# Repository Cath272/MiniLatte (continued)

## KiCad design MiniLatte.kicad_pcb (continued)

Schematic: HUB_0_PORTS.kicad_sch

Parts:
C19, C20, C21, C22, C23, C24, C25, C26: 100nF; C_0402_1005Metric
C85, C86, C87: 220uF; C_Elec_6.3x7.7
D11, D12, D13, D14: RCLAMP0524P-N; DFN-10L_L2.5-W1.0-P0.50-BL; LCSC Part C316044
R11: 120k; R_0402_1005Metric
R12, R13: 10k; R_0402_1005Metric
R27, R28: ?k; R_0402_1005Metric
U3: VL162; MQFN-28_L4.5-W3.5-P0.40-BL-EP; LCSC Part C19270896
U8: TPS2560DRCR; VSON-10_L3.0-W3.0-P0.50-BL-EP_TPS62410DRCR; LCSC Part C140304
U9: TPS2553DRVR-1; WSON-6_L2.0-W2.0-P0.65-BL-EP; LCSC Part C411878
USB1: TYPEC-324-BCP24; USB-C-SMD_TYPEC-324-BCP24; LCSC Part C2835314
USB2, USB3: U-A-39WD-W-1; USB-A-SMD_U-A-39WD-W-1; LCSC Part C3020886

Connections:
+5V: U3.25 (CE), U3.26 (VCC5V), U3.27 (Vconn_5Vin), U8.2 (IN), U8.3 (IN), U9.6 (IN); also elsewhere on the board
+5V_DFP2: C87.1, USB1.A4 (VBUS), USB1.A9 (VBUS), USB1.B4 (VBUS), USB1.B9 (VBUS); also elsewhere on the board
+5V_DFP3: C85.1, USB3.1 (VBUS); also elsewhere on the board
+5V_DFP4: C86.1, USB2.1 (VBUS); also elsewhere on the board
+5V_H0_DFP1: U8.9 (OUT1)
+5V_H0_DFP2: U8.8 (OUT2)
+5V_H0_DFP3: U9.1 (OUT)
/USB_3/USB_HUB_0/HUB_0_PORTS/DFP2TX1+: C19.2, U3.2 (TX1_P)
/USB_3/USB_HUB_0/HUB_0_PORTS/DFP2TX1-: C20.1, U3.3 (TX1_N)
/USB_3/USB_HUB_0/HUB_0_PORTS/DFP2TX2+: C22.1, U3.5 (TX2_P)
/USB_3/USB_HUB_0/HUB_0_PORTS/DFP2TX2-: C21.2, U3.4 (TX2_N)
/USB_3/USB_HUB_0/HUB_0_PORTS/DFP2_D+: USB1.A6 (DP1), USB1.B6 (DP2); also elsewhere on the board
/USB_3/USB_HUB_0/HUB_0_PORTS/DFP2_D-: USB1.A7 (DN1), USB1.B7 (DN2); also elsewhere on the board
/USB_3/USB_HUB_0/HUB_0_PORTS/DFP2_RX+: U3.18 (RX_P); also elsewhere on the board
/USB_3/USB_HUB_0/HUB_0_PORTS/DFP2_RX-: U3.17 (RX_N); also elsewhere on the board
/USB_3/USB_HUB_0/HUB_0_PORTS/DFP2_TX+: U3.21 (TXP); also elsewhere on the board
/USB_3/USB_HUB_0/HUB_0_PORTS/DFP2_TX-: U3.20 (TXN); also elsewhere on the board
/USB_3/USB_HUB_0/HUB_0_PORTS/DFP3_D+: USB3.3 (D+); also elsewhere on the board
/USB_3/USB_HUB_0/HUB_0_PORTS/DFP3_D-: USB3.2 (D-); also elsewhere on the board
/USB_3/USB_HUB_0/HUB_0_PORTS/DFP3_RX+: D13.2, D13.9, USB3.6 (STDA_SSRX+); also elsewhere on the board
/USB_3/USB_HUB_0/HUB_0_PORTS/DFP3_RX-: D13.1, D13.10, USB3.5 (STDA_SSRX-); also elsewhere on the board
/USB_3/USB_HUB_0/HUB_0_PORTS/DFP3_TX+: C26.2; also elsewhere on the board
/USB_3/USB_HUB_0/HUB_0_PORTS/DFP3_TX-: C25.1; also elsewhere on the board
/USB_3/USB_HUB_0/HUB_0_PORTS/DFP4_D+: USB2.3 (D+); also elsewhere on the board
/USB_3/USB_HUB_0/HUB_0_PORTS/DFP4_D-: USB2.2 (D-); also elsewhere on the board
/USB_3/USB_HUB_0/HUB_0_PORTS/DFP4_RX+: D14.2, D14.9, USB2.6 (STDA_SSRX+); also elsewhere on the board
/USB_3/USB_HUB_0/HUB_0_PORTS/DFP4_RX-: D14.1, D14.10, USB2.5 (STDA_SSRX-); also elsewhere on the board
/USB_3/USB_HUB_0/HUB_0_PORTS/DFP4_TX+: C24.2; also elsewhere on the board
/USB_3/USB_HUB_0/HUB_0_PORTS/DFP4_TX-: C23.1; also elsewhere on the board
/USB_3/USB_HUB_0/HUB_0_PORTS/H0_DFP3TXC+: C26.1, D13.5, D13.6, USB3.9 (STDA_SSTX+)
/USB_3/USB_HUB_0/HUB_0_PORTS/H0_DFP3TXC-: C25.2, D13.4, D13.7, USB3.8 (STDA_SSTX-)
/USB_3/USB_HUB_0/HUB_0_PORTS/H0_DFP4TXC+: C24.1, D14.5, D14.6, USB2.9 (STDA_SSTX+)
/USB_3/USB_HUB_0/HUB_0_PORTS/H0_DFP4TXC-: C23.2, D14.4, D14.7, USB2.8 (STDA_SSTX-)
DFP2_H0_RX_1+: D11.1, D11.10, U3.6 (RX1_P), USB1.B11 (SSRXp1)
DFP2_H0_RX_1-: D11.2, D11.9, U3.7 (RX1_N), USB1.B10 (SSRXn1)
DFP2_H0_RX_2+: D12.5, D12.6, U3.9 (RX2_P), USB1.A11 (SSRXp2)
DFP2_H0_RX_2-: D12.4, D12.7, U3.8 (RX2_N), USB1.A10 (SSRXn2)
DFP2_H0_TX_1+: D12.1, D12.10, USB1.A2 (SSTXP1)
DFP2_H0_TX_1-: D12.2, D12.9, USB1.A3 (SSTXn1)
DFP2_H0_TX_2+: D11.5, D11.6, USB1.B2 (SSTXp2)
DFP2_H0_TX_2-: D11.4, D11.7, USB1.B3 (SSTXn2)
DFP2_TX_1+: C19.1
DFP2_TX_1-: C20.2
DFP2_TX_2+: C22.2
DFP2_TX_2-: C21.1
GND: C85.2, C86.2, C87.2, D11.3, D11.8, D12.3, D12.8, D13.3, D13.8, D14.3, D14.8, R11.1, R12.2, R13.2, R27.1, R28.1, U3.19 (GND), U3.29 (EP), U8.1 (GND), U8.11 (EPAD), U9.5 (GND), U9.7 (EP), USB1.1 (EP), USB1.2 (EP), USB1.3 (EP), USB1.4 (EP), USB1.A1 (GND), USB1.A12 (GND), USB1.B1 (GND), USB1.B12 (GND), USB2.4 (GND), USB2.7 (GND_DRAIN), USB2.10 (EP), USB2.11 (EP), USB3.4 (GND), USB3.7 (GND_DRAIN), USB3.10 (EP), USB3.11 (EP); also elsewhere on the board
H0_CC1_DFP2: U3.1 (CC1), USB1.A5 (CC1)
H0_CC2_DFP2: U3.28 (CC2), USB1.B5 (CC2)
H0_USBOC1: U8.10 (~FAULT1)
H0_USBOC2: U8.6 (~FAULT2); also elsewhere on the board
H0_USBOC3: U9.3 (~FAULT); also elsewhere on the board
H0_USBPE1: U8.4 (EN1)
H0_USBPE2: U8.5 (EN2); also elsewhere on the board
H0_USBPE3: U9.4 (EN); also elsewhere on the board
unnamed: R12.1, U3.24 (CurrentSettingin<0>)
unnamed: R13.1, U3.23 (CurrentSettingin<1>)
unnamed: R11.2, U3.10 (REXT)
unnamed: R27.2, U8.7 (ILIM)
unnamed: R28.2, U9.2 (ILIM)

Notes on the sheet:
TO ADD CAPS ON TX LINES + TO ADD TVS DIODE

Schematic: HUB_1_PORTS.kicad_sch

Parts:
C88, C89: 220uF; C_Elec_6.3x7.7
C120, C121, C122, C123, C124, C125, C126, C127, C166, C174, C175, C176: 100nF; C_0402_1005Metric
D15, D16: RCLAMP0524P-N; DFN-10L_L2.5-W1.0-P0.50-BL; LCSC Part C316044
R54, R107: 120k; R_0402_1005Metric
R55, R56, R108, R109: 10k; R_0402_1005Metric
R111, R112: ?k; R_0402_1005Metric
U13, U18: VL162; MQFN-28_L4.5-W3.5-P0.40-BL-EP; LCSC Part C19270896
U20, U21: TPS2560DRCR; VSON-10_L3.0-W3.0-P0.50-BL-EP_TPS62410DRCR; LCSC Part C140304
USB9: USB-303WSD-BRY; USB-A-TH_XUNPU_USB-303WSD-BRY; LCSC Part C2895028

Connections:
+5V: U13.25 (CE), U13.26 (VCC5V), U13.27 (Vconn_5Vin), U18.25 (CE), U18.26 (VCC5V), U18.27 (Vconn_5Vin), U20.2 (IN), U20.3 (IN), U21.2 (IN), U21.3 (IN); also elsewhere on the board
+5V_DFP3: C89.1, USB9.10 (VBUS2); also elsewhere on the board
+5V_DFP4: C88.1, USB9.1 (VBUS1); also elsewhere on the board
+5V_H1_DFP1: U20.9 (OUT1)
+5V_H1_DFP2: U20.8 (OUT2)
+5V_H1_DFP3: U21.9 (OUT1)
+5V_H1_DFP4: U21.8 (OUT2)
/USB_3/USB_HUB_1/HUB_1_PORTS/DFP1_RX+: U18.18 (RX_P); also elsewhere on the board
/USB_3/USB_HUB_1/HUB_1_PORTS/DFP1_RX-: U18.17 (RX_N); also elsewhere on the board
/USB_3/USB_HUB_1/HUB_1_PORTS/DFP1_TX+: U18.21 (TXP); also elsewhere on the board
/USB_3/USB_HUB_1/HUB_1_PORTS/DFP1_TX-: U18.20 (TXN); also elsewhere on the board
/USB_3/USB_HUB_1/HUB_1_PORTS/DFP2_RX+: U13.18 (RX_P); also elsewhere on the board
/USB_3/USB_HUB_1/HUB_1_PORTS/DFP2_RX-: U13.17 (RX_N); also elsewhere on the board
/USB_3/USB_HUB_1/HUB_1_PORTS/DFP2_TX+: U13.21 (TXP); also elsewhere on the board
/USB_3/USB_HUB_1/HUB_1_PORTS/DFP2_TX-: U13.20 (TXN); also elsewhere on the board
/USB_3/USB_HUB_1/HUB_1_PORTS/DFP3_D+: USB9.12 (D2+); also elsewhere on the board
/USB_3/USB_HUB_1/HUB_1_PORTS/DFP3_D-: USB9.11 (D2-); also elsewhere on the board
/USB_3/USB_HUB_1/HUB_1_PORTS/DFP3_RX+: D15.2, D15.9, USB9.15 (StdA_SSRX2+); also elsewhere on the board
/USB_3/USB_HUB_1/HUB_1_PORTS/DFP3_RX-: D15.1, D15.10, USB9.14 (StdA_SSRX2-); also elsewhere on the board
/USB_3/USB_HUB_1/HUB_1_PORTS/DFP3_TX+: C127.2; also elsewhere on the board
/USB_3/USB_HUB_1/HUB_1_PORTS/DFP3_TX-: C126.1; also elsewhere on the board
/USB_3/USB_HUB_1/HUB_1_PORTS/DFP4_D+: USB9.3 (D1+); also elsewhere on the board
/USB_3/USB_HUB_1/HUB_1_PORTS/DFP4_D-: USB9.2 (D1-); also elsewhere on the board
/USB_3/USB_HUB_1/HUB_1_PORTS/DFP4_RX+: D16.2, D16.9, USB9.6 (StdA_SSRX1+); also elsewhere on the board
/USB_3/USB_HUB_1/HUB_1_PORTS/DFP4_RX-: D16.1, D16.10, USB9.5 (StdA_SSRX1-); also elsewhere on the board
/USB_3/USB_HUB_1/HUB_1_PORTS/DFP4_TX+: C125.2; also elsewhere on the board
/USB_3/USB_HUB_1/HUB_1_PORTS/DFP4_TX-: C124.1; also elsewhere on the board
/USB_3/USB_HUB_1/HUB_1_PORTS/H1_DFP1TX1+: C166.2, U18.2 (TX1_P)
/USB_3/USB_HUB_1/HUB_1_PORTS/H1_DFP1TX1-: C174.1, U18.3 (TX1_N)
/USB_3/USB_HUB_1/HUB_1_PORTS/H1_DFP1TX2+: C176.1, U18.5 (TX2_P)
/USB_3/USB_HUB_1/HUB_1_PORTS/H1_DFP1TX2-: C175.2, U18.4 (TX2_N)
/USB_3/USB_HUB_1/HUB_1_PORTS/H1_DFP2TX1+: C120.2, U13.2 (TX1_P)
/USB_3/USB_HUB_1/HUB_1_PORTS/H1_DFP2TX1-: C121.1, U13.3 (TX1_N)
/USB_3/USB_HUB_1/HUB_1_PORTS/H1_DFP2TX2+: C123.1, U13.5 (TX2_P)
/USB_3/USB_HUB_1/HUB_1_PORTS/H1_DFP2TX2-: C122.2, U13.4 (TX2_N)
/USB_3/USB_HUB_1/HUB_1_PORTS/H1_DFP3TXC+: C127.1, D15.5, D15.6, USB9.18 (StdA_SSTX2+)
/USB_3/USB_HUB_1/HUB_1_PORTS/H1_DFP3TXC-: C126.2, D15.4, D15.7, USB9.17 (StdA_SSTX2-)
/USB_3/USB_HUB_1/HUB_1_PORTS/H1_DFP4TXC+: C125.1, D16.5, D16.6, USB9.9 (StdA_SSTX1+)
/USB_3/USB_HUB_1/HUB_1_PORTS/H1_DFP4TXC-: C124.2, D16.4, D16.7, USB9.8 (StdA_SSTX1-)
GND: C88.2, C89.2, D15.3, D15.8, D16.3, D16.8, R54.1, R55.2, R56.2, R107.1, R108.2, R109.2, R111.1, R112.1, U13.19 (GND), U13.29 (EP), U18.19 (GND), U18.29 (EP), U20.1 (GND), U20.11 (EPAD), U21.1 (GND), U21.11 (EPAD), USB9.4 (GND1), USB9.7 (GND_DRAIN1), USB9.13 (GND2), USB9.16 (GND_DRAIN2), USB9.19 (Shield), USB9.20 (Shield), USB9.21 (Shield), USB9.22 (Shield); also elsewhere on the board
H1_CC1_DFP1: U18.1 (CC1); also elsewhere on the board
H1_CC1_DFP2: U13.1 (CC1); also elsewhere on the board
H1_CC2_DFP1: U18.28 (CC2); also elsewhere on the board
H1_CC2_DFP2: U13.28 (CC2); also elsewhere on the board
H1_DFP1_RX_1+: U18.6 (RX1_P); also elsewhere on the board
H1_DFP1_RX_1-: U18.7 (RX1_N); also elsewhere on the board
H1_DFP1_RX_2+: U18.9 (RX2_P); also elsewhere on the board
H1_DFP1_RX_2-: U18.8 (RX2_N); also elsewhere on the board
H1_DFP1_TX_1+: C166.1; also elsewhere on the board
H1_DFP1_TX_1-: C174.2; also elsewhere on the board
H1_DFP1_TX_2+: C176.2; also elsewhere on the board
H1_DFP1_TX_2-: C175.1; also elsewhere on the board
H1_DFP2_RX_1+: U13.6 (RX1_P); also elsewhere on the board
H1_DFP2_RX_1-: U13.7 (RX1_N); also elsewhere on the board
H1_DFP2_RX_2+: U13.9 (RX2_P); also elsewhere on the board
H1_DFP2_RX_2-: U13.8 (RX2_N); also elsewhere on the board
H1_DFP2_TX_1+: C120.1; also elsewhere on the board
H1_DFP2_TX_1-: C121.2; also elsewhere on the board
H1_DFP2_TX_2+: C123.2; also elsewhere on the board
H1_DFP2_TX_2-: C122.1; also elsewhere on the board
H1_USBOC1: U20.10 (~FAULT1)
H1_USBOC2: U20.6 (~FAULT2); also elsewhere on the board
H1_USBOC3: U21.10 (~FAULT1); also elsewhere on the board
H1_USBOC4: U21.6 (~FAULT2); also elsewhere on the board
H1_USBPE1: U20.4 (EN1)
H1_USBPE2: U20.5 (EN2); also elsewhere on the board
H1_USBPE3: U21.4 (EN1); also elsewhere on the board
H1_USBPE4: U21.5 (EN2); also elsewhere on the board
unnamed: R55.1, U13.24 (CurrentSettingin<0>)
unnamed: R56.1, U13.23 (CurrentSettingin<1>)
unnamed: R54.2, U13.10 (REXT)
unnamed: R108.1, U18.24 (CurrentSettingin<0>)
unnamed: R109.1, U18.23 (CurrentSettingin<1>)
unnamed: R107.2, U18.10 (REXT)
unnamed: R111.2, U20.7 (ILIM)
unnamed: R112.2, U21.7 (ILIM)

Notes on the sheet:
TO ADD CAPS ON TX LINES + TO ADD TVS DIODE

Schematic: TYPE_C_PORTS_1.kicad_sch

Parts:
C90, C91: 220uF; C_Elec_6.3x7.7
D7, D8, D9, D10: RCLAMP0524P-N; DFN-10L_L2.5-W1.0-P0.50-BL; LCSC Part C316044
USB4, USB7: TYPEC-324-BCP24; USB-C-SMD_TYPEC-324-BCP24; LCSC Part C2835314

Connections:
+5V_DFP1: C91.1, USB7.A4 (VBUS), USB7.A9 (VBUS), USB7.B4 (VBUS), USB7.B9 (VBUS)
+5V_DFP2: C90.1, USB4.A4 (VBUS), USB4.A9 (VBUS), USB4.B4 (VBUS), USB4.B9 (VBUS); also elsewhere on the board
/USB_3/USB_HUB_1/HUB_1_PORTS/DFP1_D+: USB7.A6 (DP1), USB7.B6 (DP2); also elsewhere on the board
/USB_3/USB_HUB_1/HUB_1_PORTS/DFP1_D-: USB7.A7 (DN1), USB7.B7 (DN2); also elsewhere on the board
/USB_3/USB_HUB_1/HUB_1_PORTS/DFP2_D+: USB4.A6 (DP1), USB4.B6 (DP2); also elsewhere on the board
/USB_3/USB_HUB_1/HUB_1_PORTS/DFP2_D-: USB4.A7 (DN1), USB4.B7 (DN2); also elsewhere on the board
GND: C90.2, C91.2, D7.3, D7.8, D8.3, D8.8, D9.3, D9.8, D10.3, D10.8, USB4.1 (EP), USB4.2 (EP), USB4.3 (EP), USB4.4 (EP), USB4.A1 (GND), USB4.A12 (GND), USB4.B1 (GND), USB4.B12 (GND), USB7.1 (EP), USB7.2 (EP), USB7.3 (EP), USB7.4 (EP), USB7.A1 (GND), USB7.A12 (GND), USB7.B1 (GND), USB7.B12 (GND); also elsewhere on the board
H1_CC1_DFP1: USB7.A5 (CC1); also elsewhere on the board
H1_CC1_DFP2: USB4.A5 (CC1); also elsewhere on the board
H1_CC2_DFP1: USB7.B5 (CC2); also elsewhere on the board
H1_CC2_DFP2: USB4.B5 (CC2); also elsewhere on the board
H1_DFP1_RX_1+: D9.1, D9.10, USB7.B11 (SSRXp1); also elsewhere on the board
H1_DFP1_RX_1-: D9.2, D9.9, USB7.B10 (SSRXn1); also elsewhere on the board
H1_DFP1_RX_2+: D10.5, D10.6, USB7.A11 (SSRXp2); also elsewhere on the board
H1_DFP1_RX_2-: D10.4, D10.7, USB7.A10 (SSRXn2); also elsewhere on the board
H1_DFP1_TX_1+: D10.1, D10.10, USB7.A2 (SSTXP1); also elsewhere on the board
H1_DFP1_TX_1-: D10.2, D10.9, USB7.A3 (SSTXn1); also elsewhere on the board
H1_DFP1_TX_2+: D9.5, D9.6, USB7.B2 (SSTXp2); also elsewhere on the board
H1_DFP1_TX_2-: D9.4, D9.7, USB7.B3 (SSTXn2); also elsewhere on the board
H1_DFP2_RX_1+: D8.1, D8.10, USB4.B11 (SSRXp1); also elsewhere on the board
H1_DFP2_RX_1-: D8.2, D8.9, USB4.B10 (SSRXn1); also elsewhere on the board
H1_DFP2_RX_2+: D8.5, D8.6, USB4.A11 (SSRXp2); also elsewhere on the board
H1_DFP2_RX_2-: D8.4, D8.7, USB4.A10 (SSRXn2); also elsewhere on the board
H1_DFP2_TX_1+: D7.1, D7.10, USB4.A2 (SSTXP1); also elsewhere on the board
H1_DFP2_TX_1-: D7.2, D7.9, USB4.A3 (SSTXn1); also elsewhere on the board
H1_DFP2_TX_2+: D7.5, D7.6, USB4.B2 (SSTXp2); also elsewhere on the board
H1_DFP2_TX_2-: D7.4, D7.7, USB4.B3 (SSTXn2); also elsewhere on the board

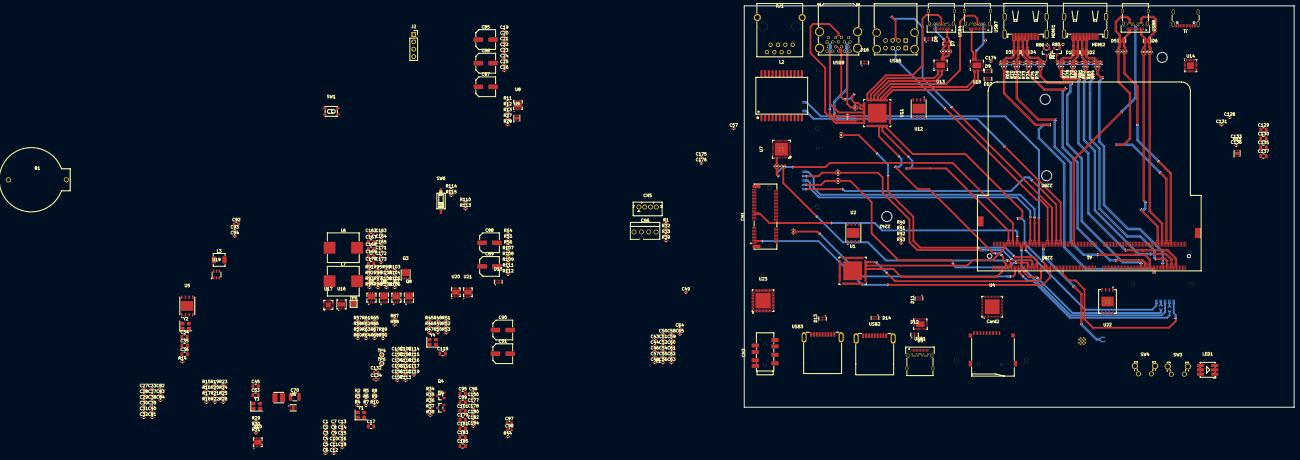
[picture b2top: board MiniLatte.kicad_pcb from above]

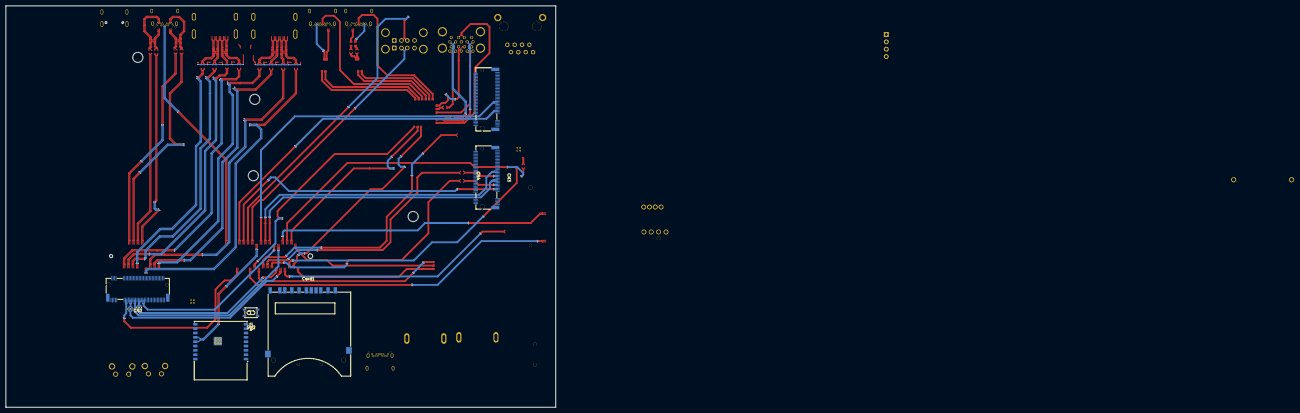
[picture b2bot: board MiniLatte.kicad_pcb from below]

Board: 4 copper layers, 189.8 x 138.6 mm, 391 parts (10 on the bottom side), 476 nets.

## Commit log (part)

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2026-03-12 redo folder structure
2026-03-13 Added LedArray and latex project
2026-04-01 Fix image links and update text in README
    Updated image links and corrected text formatting in README.
